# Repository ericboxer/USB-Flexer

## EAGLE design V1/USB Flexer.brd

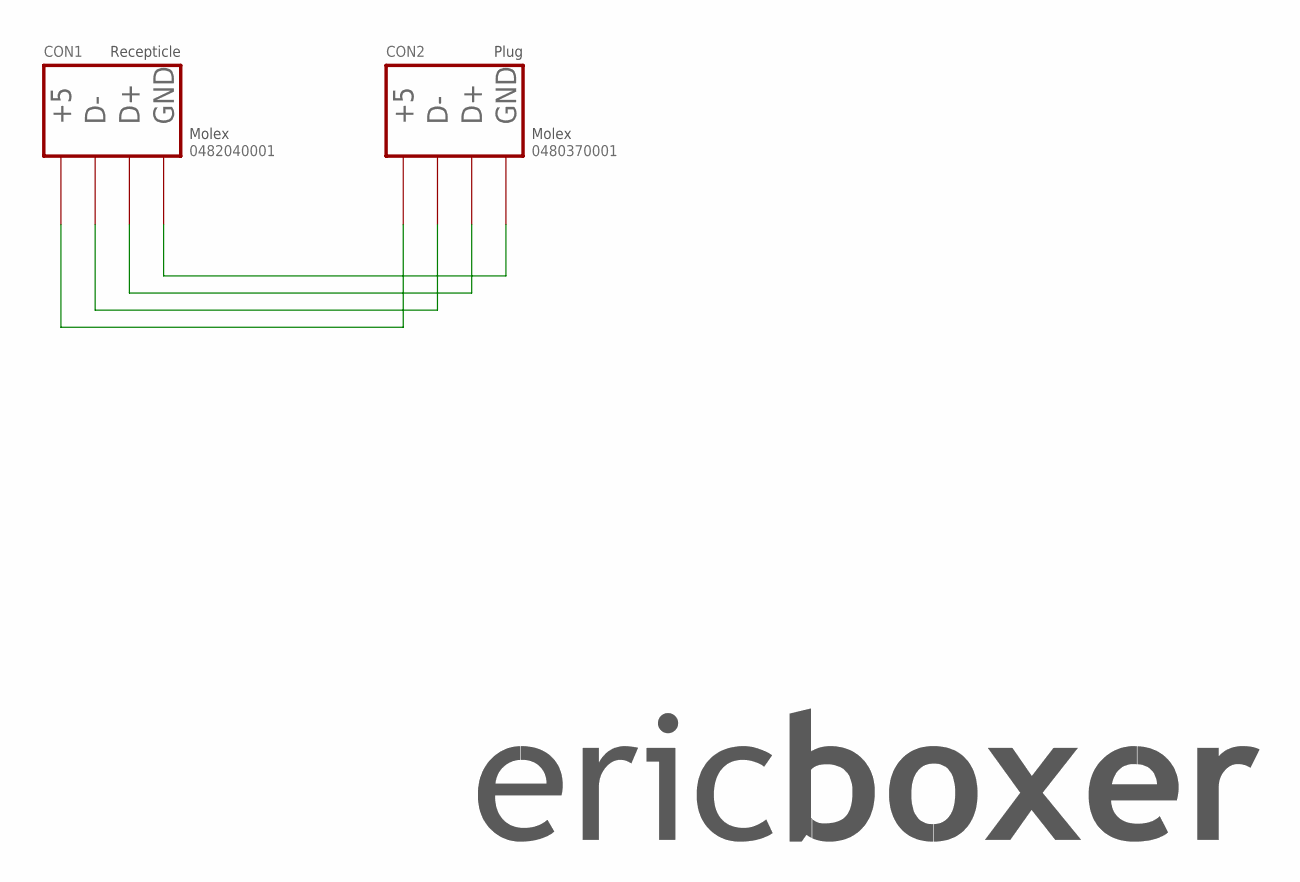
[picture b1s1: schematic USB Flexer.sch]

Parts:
CON1: USB_RECEPTICLE; MOLEX_0482040001_RIGHT_ANGLE_RECEPTACLE
CON2: USB_PLUG; MOLEX_0480370001_PLUG_TYPE_A
U$1: ERIC_BOXER_LOGO20; BOXER_SHORTS_20MM

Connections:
GND: CON1.GND, CON1.GND@1 (GND), CON1.GND@2 (GND), CON1.GND@3 (GND), CON1.GND@4 (GND), CON2.GND, CON2.GND@1 (GND), CON2.GND@2 (GND)
unnamed: CON1.5V (+5), CON2.5+ (+5)
unnamed: CON1.D-, CON2.D-
unnamed: CON1.D+, CON2.D+

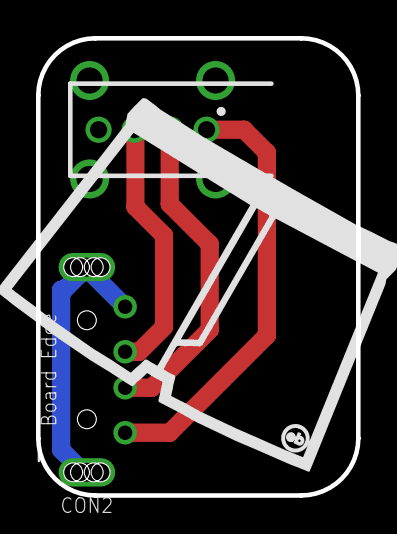
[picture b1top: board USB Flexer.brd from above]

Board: 2 copper layers, 17.8 x 25.4 mm, 3 parts (0 on the bottom side), 4 nets.

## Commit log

2016-01-20 First
